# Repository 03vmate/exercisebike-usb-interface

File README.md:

# exbike-usb-interface
AVR MCU based USB interface for exercise bike

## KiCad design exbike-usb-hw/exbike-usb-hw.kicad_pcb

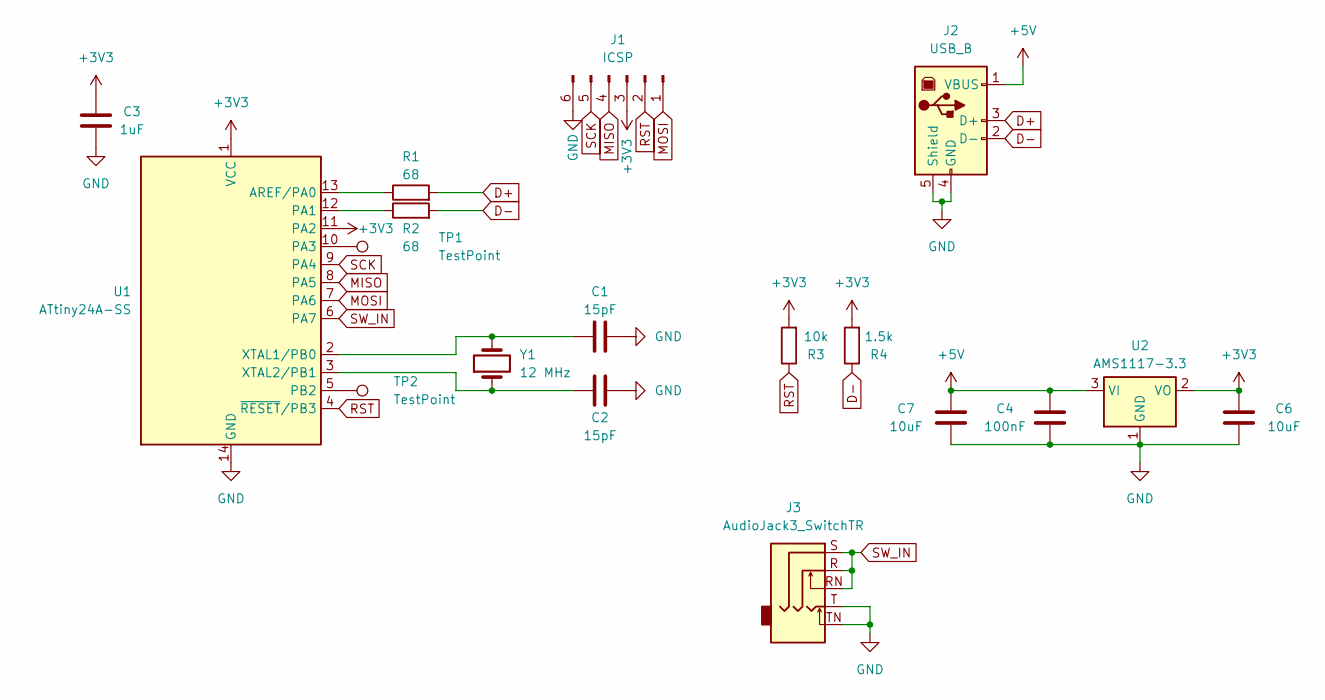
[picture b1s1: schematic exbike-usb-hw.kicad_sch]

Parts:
C1, C2: 15pF; C_0805_2012Metric_Pad1.18x1.45mm_HandSolder
C3: 1uF; C_0805_2012Metric_Pad1.18x1.45mm_HandSolder
C4: 100nF; C_0805_2012Metric_Pad1.18x1.45mm_HandSolder
C6, C7: 10uF; C_0805_2012Metric_Pad1.18x1.45mm_HandSolder
J1: ICSP; PinHeader_1x06_P2.54mm_Vertical
J2: USB_B; USB_B_Lumberg_2411_02_Horizontal
J3: AudioJack3_SwitchTR; Jack_3.5mm_Ledino_KB3SPRS_Horizontal
R1, R2: 68; R_0805_2012Metric_Pad1.20x1.40mm_HandSolder
R3: 10k; R_0805_2012Metric_Pad1.20x1.40mm_HandSolder
R4: 1.5k; R_0805_2012Metric_Pad1.20x1.40mm_HandSolder
TP1: TestPoint; TestPoint_Pad_D1.5mm
TP2: TestPoint; TestPoint_Pad_D1.0mm
U1: ATtiny24A-SS; SOIC-14_3.9x8.7mm_P1.27mm
U2: AMS1117-3.3; SOT-223-3_TabPin2
Y1: 12 MHz; Crystal_HC49-4H_Vertical

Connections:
+3V3: C3.1, C6.1, J1.3, R3.2, R4.2, U1.1 (VCC), U1.11 (PA2), U2.2 (VO)
+5V: C4.1, C7.1, J2.1 (VBUS), U2.3 (VI)
D+: J2.3 (D+), R1.2
D-: J2.2 (D-), R2.2, R4.1
GND: C1.2, C2.2, C3.2, C4.2, C6.2, C7.2, J1.6, J2.4 (GND), J2.5 (Shield), J3.T, J3.TN, U1.14 (GND), U2.1 (GND)
MISO: J1.4, U1.8 (PA5)
MOSI: J1.1, U1.7 (PA6)
unnamed: R1.1, U1.13 (AREF/PA0)
unnamed: R2.1, U1.12 (PA1)
unnamed: TP1.1, U1.10 (PA3)
unnamed: TP2.1, U1.5 (PB2)
unnamed: C1.1, U1.2 (XTAL1/PB0), Y1.2
unnamed: C2.1, U1.3 (XTAL2/PB1), Y1.1
RST: J1.2, R3.1, U1.4 (~RESET/PB3)
SCK: J1.5, U1.9 (PA4)
SW_IN: J3.R, J3.RN, J3.S, U1.6 (PA7)

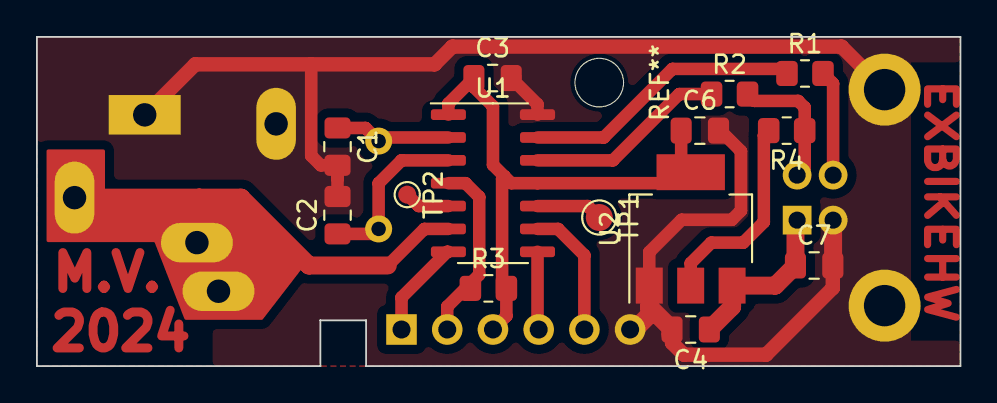
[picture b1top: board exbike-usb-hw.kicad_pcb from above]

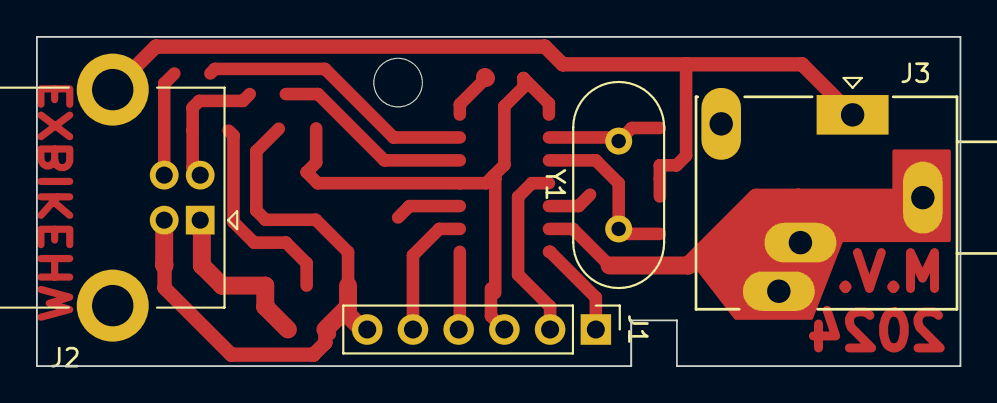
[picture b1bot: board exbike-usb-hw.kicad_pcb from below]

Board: 2 copper layers, 51.3 x 18.3 mm, 18 parts (4 on the bottom side), 16 nets.

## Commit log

2024-01-31 Schematic
2024-01-31 Layout
2024-01-31 Add d- pullup:
2024-02-11 Early USB code, PCB project cleanup
2024-02-11 Update gitignore
2024-02-12 Host side code
2024-02-12 Enclosure model
